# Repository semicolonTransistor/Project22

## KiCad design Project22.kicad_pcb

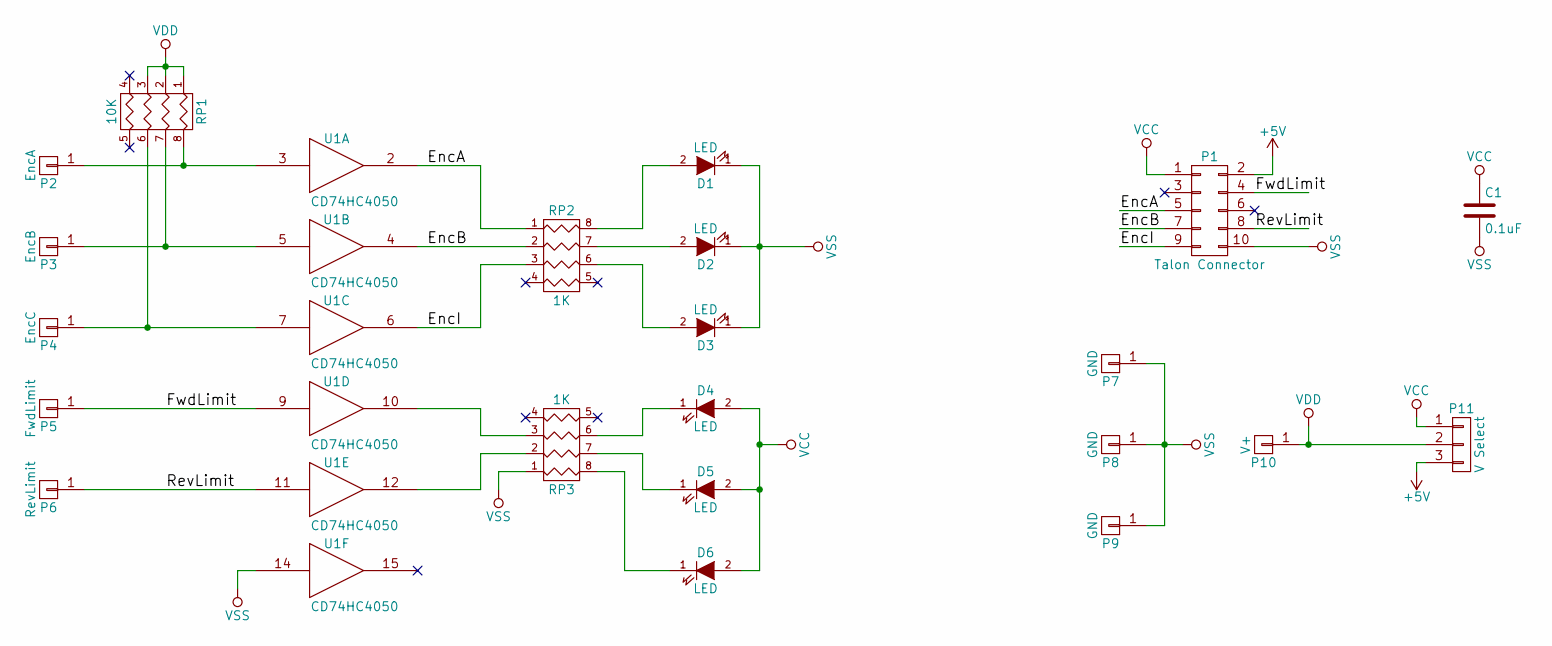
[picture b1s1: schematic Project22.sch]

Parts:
C1: 0.1uF; C_1206_HandSoldering
D1, D2, D3, D4, D5, D6: LED; LED_0805_HandSoldering
P1: Talon Connector; TalonSensorPort
P2: EncA; SolderPad
P3: EncB; SolderPad
P4: EncC; SolderPad
P5: FwdLimit; SolderPad
P6: RevLimit; SolderPad
P7, P8, P9: GND; SolderPad
P10: V+; SolderPad
P11: V Select; Pin_Header_Straight_1x03_Pitch1.00mm_SMD_Pin1Left
RP1: 10K; R_Array_Convex_4x0603
RP2, RP3: 1K; R_Array_Convex_4x0603
U1: CD74HC4050; SOIC-16_3.9x9.9mm_Pitch1.27mm

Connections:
+5V: P1.2, P11.3
/EncA: P1.5, RP2.1, U1.2
/EncB: P1.7, RP2.2, U1.4
/EncI: P1.9, RP2.3, U1.6
/FwdLimit: P1.4, P5.1, U1.9
/RevLimit: P1.8, P6.1, U1.11
unnamed: D1.2 (A), RP2.8 (R1)
unnamed: D2.2 (A), RP2.7 (R2)
unnamed: D3.2 (A), RP2.6 (R3)
unnamed: D4.1 (K), RP3.6 (R3)
unnamed: D5.1 (K), RP3.7 (R2)
unnamed: D6.1 (K), RP3.8 (R1)
unnamed: P2.1, RP1.8 (R1), U1.3
unnamed: P3.1, RP1.7 (R2), U1.5
unnamed: P4.1, RP1.6 (R3), U1.7
unnamed: RP3.2, U1.12
unnamed: RP3.3, U1.10
VCC: C1.1, D4.2 (A), D5.2 (A), D6.2 (A), P1.1, P11.1, U1.1 (VCC)
VDD: P10.1, P11.2, RP1.1, RP1.2, RP1.3
VSS: C1.2, D1.1 (K), D2.1 (K), D3.1 (K), P1.10, P7.1, P8.1, P9.1, RP3.1, U1.8 (VSS), U1.14

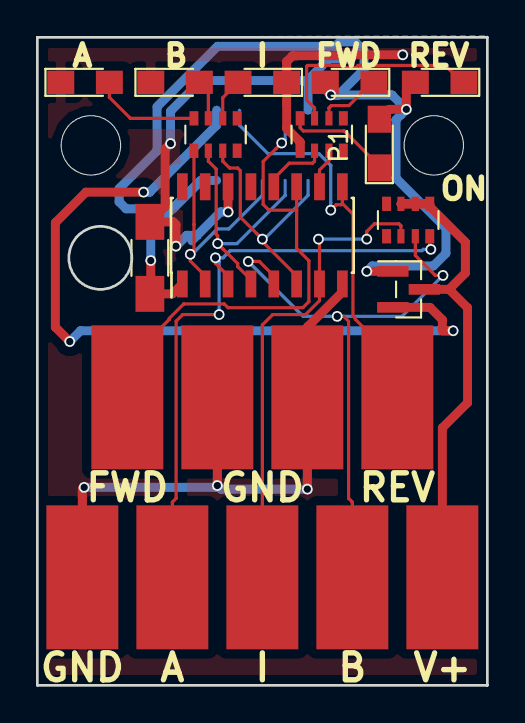
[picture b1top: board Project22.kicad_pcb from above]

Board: 2 copper layers, 25.0 x 36.0 mm, 22 parts (0 on the bottom side), 20 nets.
